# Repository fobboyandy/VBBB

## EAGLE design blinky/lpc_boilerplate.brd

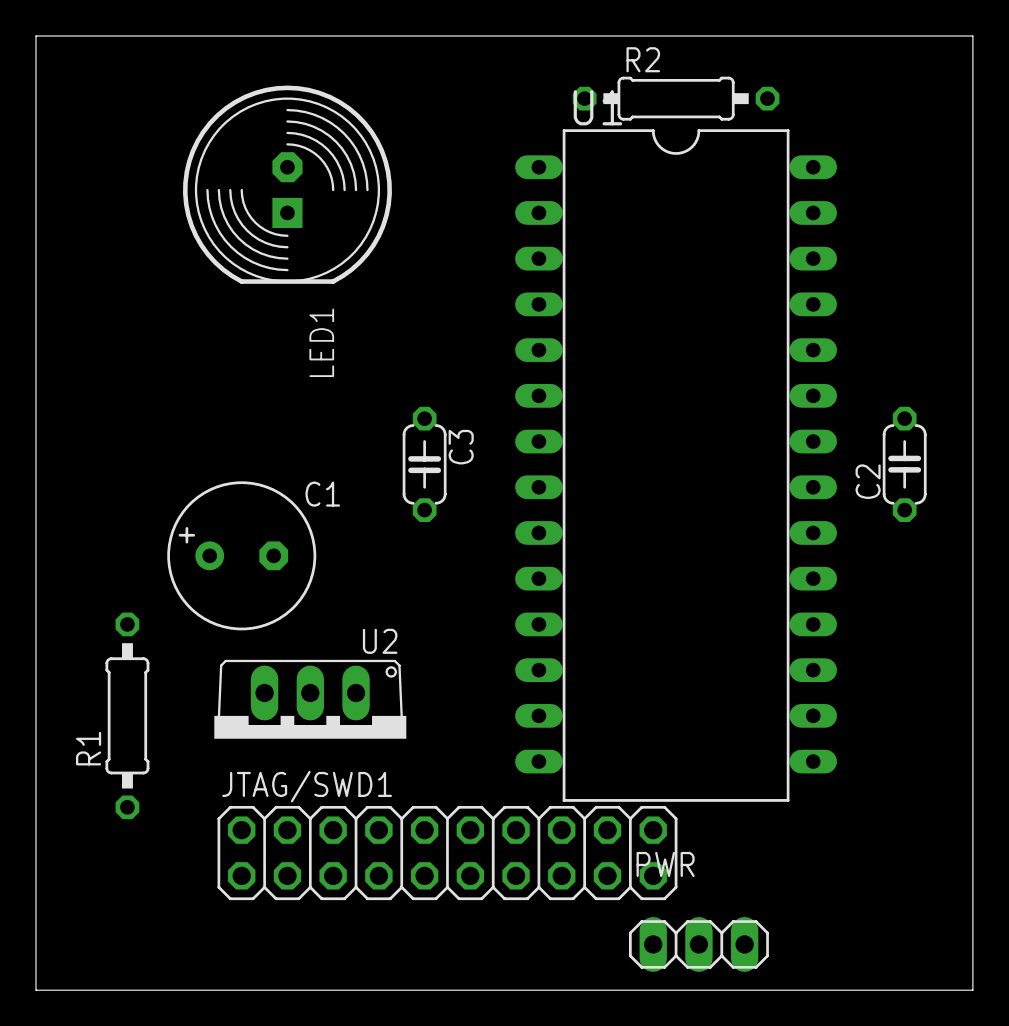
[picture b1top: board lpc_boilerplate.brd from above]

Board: 2 copper layers, 52.0 x 53.0 mm, 10 parts (0 on the bottom side), 8 nets, no tracks yet.

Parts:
C1: 47u; E3,5-8
C2, C3: .1u; C050-024X044
JTAG/SWD1: 2X10
LED1: LED10MM
PWR: 1X03
R1: 4K7; 0207/10
R2: 50; 0207/10
U1: LPC1114FN28/102; DIL28-6
U2: UA78MC; TO220V

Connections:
+3V3: C1.+, C2.1, C3.1, LED1.A, R1.2, U1.7, U1.21, U2.3
GND: C1.-, C2.2, C3.2, JTAG/SWD1.4, JTAG/SWD1.6, JTAG/SWD1.8, JTAG/SWD1.10, JTAG/SWD1.12, JTAG/SWD1.14, JTAG/SWD1.16, JTAG/SWD1.18, JTAG/SWD1.20, PWR.2, U1.8, U1.22, U2.2
unnamed: LED1.K, R2.2
unnamed: PWR.1, U2.1
unnamed: R2.1, U1.28
RESET: JTAG/SWD1.15, R1.1, U1.23
SWCLK: JTAG/SWD1.9, U1.3
SWDIO: JTAG/SWD1.7, U1.12

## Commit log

2016-08-29 :confetti_ball: Added .gitattributes & .gitignore files
2016-08-30 grabs maze from video stream and generates a maze structure in matrix form. added a DFS. todo: add a BFS for shortest path
2016-09-01 ability to create maze structure from picture and solve for shortest path using BFS
2016-09-01 file organization.
2016-09-02 Cleaned up code and fixed unsigned int issue in mazeSolver
2016-09-06 Started the code for the maze controller
2016-09-24 added multipleObjectTracking.cpp which contains a new class ball definition
    todo: create separate file for ball class
2016-11-08 added object positioning; todo: use position to direct the ball to a destination
2016-11-08 Revert "added object positioning; todo: use position to direct the ball to a destination"
    This reverts commit 360395bb407505c0005f1e81b11ef5b1a022dab6.
2016-11-08 Revert "Revert "added object positioning; todo: use position to direct the ball to a destination""
    This reverts commit b4f079290c531124aff0f8c8fd20cebd60efd703.
2016-11-16 added relative servo positioning and also serial communication
2016-11-17 added PID
2016-11-17 added pid and servo controller
